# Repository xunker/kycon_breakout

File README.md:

Breakout boards for Kycon© Connectors
=====================================

[KPJX-4S](kpjx-4s_breakout/) - Configurable Breakout Board for KJPS-4S and 4S-S.

##### License and trademarks

License information can be found in [LICENSE](LICENSE).

"Kycon" is a registered trade name of Kycon, Inc.

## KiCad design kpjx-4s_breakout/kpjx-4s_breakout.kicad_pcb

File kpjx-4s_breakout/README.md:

Kycon© KPJX-4S Connector Breakout
=================================

[Schematic](images/kpjx-4s_breakout.pdf)

Mounting holes are M2.2.

## Configuration Jumpers

Use Jumper Blocks J3-J6 to map the pins from the Kycon connector to the outgoing header J2.

For example, to make Kycon pin 1 connect to J2 output pin A, pin 2 to output pin
B, pin 3 to output C, and pin 4 to GND:

Block            | Row        | State
-----------------|------------|------
J3 (Kycon pin 1) |            |
_                | 1-2 (A)    | Closed (Jumpered)
_                | 3-4 (B)    | open
_                | 5-6 (C)    | open
_                | 7-8 (GND)  | open
J4 (Kycon pin 2) |            |
_                | 1-2 (A)    | open
_                | 3-4 (B)    | Closed (Jumpered)
_                | 5-6 (C)    | open
_                | 7-8 (GND)  | open
J5 (Kycon pin 3) |            |
_                | 1-2 (A)    | open
_                | 3-4 (B)    | open
_                | 5-6 (C)    | Closed (Jumpered)
_                | 7-8 (GND)  | open
J6 (Kycon pin 4) |            |
_                | 1-2 (A)    | open
_                | 3-4 (B)    | open
_                | 5-6 (C)    | open
_                | 7-8 (GND)  | Closed (Jumpered)

Multiple Kycon pins can be connected to the same output, as long as they are the
same voltage. For example, If power coming in to the Kycon connector as +12V on
pins 1 and 3, and ground on pins 2 and 4, I could configure J3-J6 as:

Block            | Row        | State
-----------------|------------|------
J3 (Kycon pin 1) |            |
_                | 1-2 (A)    | Closed (Jumpered)
_                | 3-4 (B)    | open
_                | 5-6 (C)    | open
_                | 7-8 (GND)  | open
J4 (Kycon pin 2) |            |
_                | 1-2 (A)    | open
_                | 3-4 (B)    | open
_                | 5-6 (C)    | open
_                | 7-8 (GND)  | Closed (Jumpered)
J5 (Kycon pin 3) |            |
_                | 1-2 (A)    | Closed (Jumpered)
_                | 3-4 (B)    | open
_                | 5-6 (C)    | open
_                | 7-8 (GND)  | open
J6 (Kycon pin 4) |            |
_                | 1-2 (A)    | open
_                | 3-4 (B)    | open
_                | 5-6 (C)    | open
_                | 7-8 (GND)  | Closed (Jumpered)

This would combine both +12V pins to a single output (A) and both GND pins to
ground. In this configuration, output pins B and C are not connected.

### Credit

[Footprint for KPJX-4S](https://github.com/prusa3d/Buddy-board-MINI-PCB/blob/master/rev.1.0.0/.pretty/KPJX-4S.kicad_mod) connector is from [Prusa3D's Buddy Board Mini PCB](https://github.com/prusa3d/Buddy-board-MINI-PCB/tree/master).

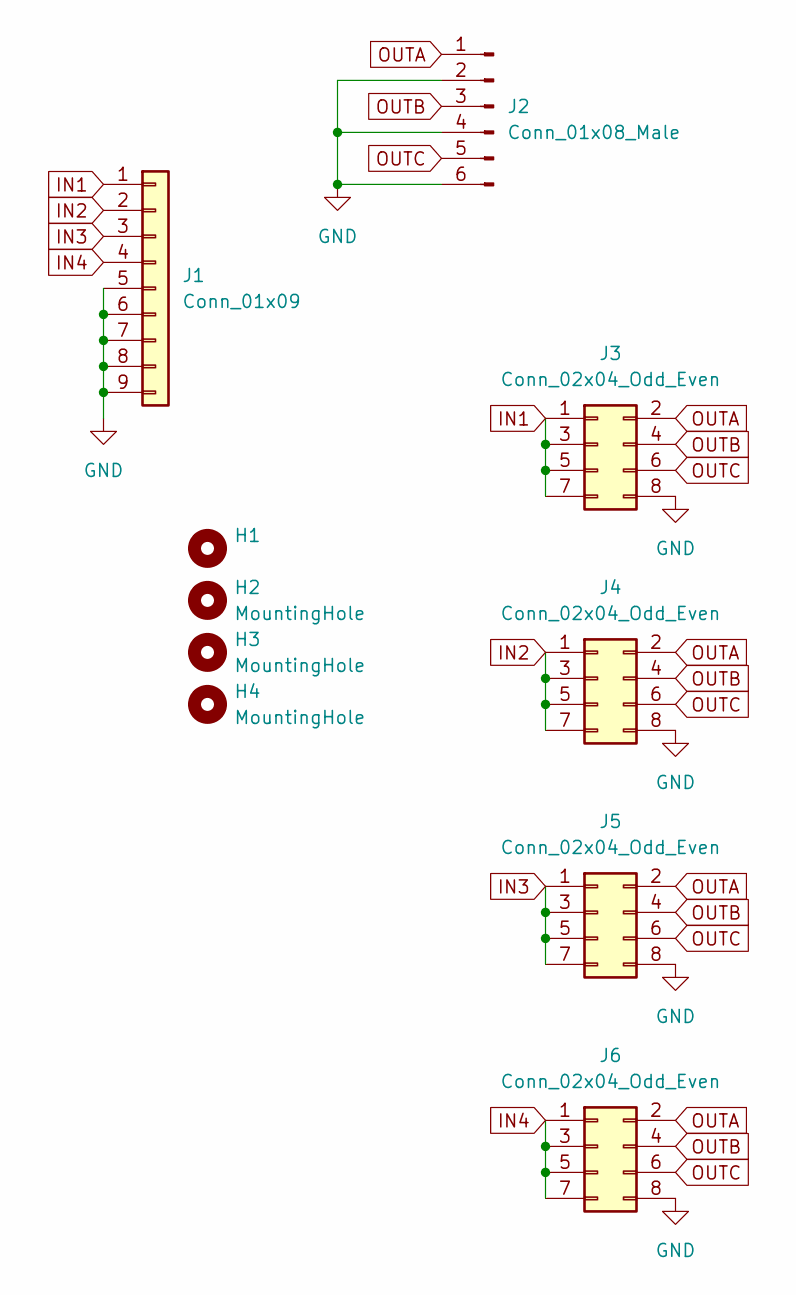
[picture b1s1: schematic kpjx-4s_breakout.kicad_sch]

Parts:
H1: (no value)
H2, H3, H4: MountingHole; MountingHole_2.2mm_M2_DIN965
J1: Conn_01x09; KPJX-4S
J2: Conn_01x08_Male; PinHeader_1x06_P2.54mm_Vertical
J3, J4, J5, J6: Conn_02x04_Odd_Even; PinHeader_2x04_P2.54mm_Vertical

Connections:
GND: J1.5, J1.6, J1.7, J1.8, J1.9, J2.2, J2.4, J2.6, J3.8, J4.8, J5.8, J6.8
IN1: J1.1, J3.1, J3.3, J3.5, J3.7
IN2: J1.2, J4.1, J4.3, J4.5, J4.7
IN3: J1.3, J5.1, J5.3, J5.5, J5.7
IN4: J1.4, J6.1, J6.3, J6.5, J6.7
OUTA: J2.1, J3.2, J4.2, J5.2, J6.2
OUTB: J2.3, J3.4, J4.4, J5.4, J6.4
OUTC: J2.5, J3.6, J4.6, J5.6, J6.6

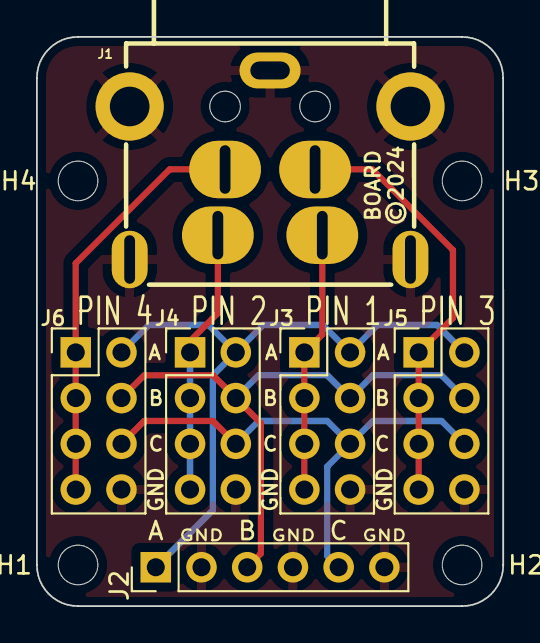
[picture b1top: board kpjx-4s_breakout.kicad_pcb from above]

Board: 2 copper layers, 25.9 x 31.6 mm, 10 parts (0 on the bottom side), 8 nets.

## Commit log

2024-06-13 add link to license
2024-06-13 add kpjs-4s from other dir
2024-06-13 Add pictures, clean up schematic
2024-06-13 fix filenames

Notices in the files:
kpjx-4s_breakout/kpjx-4s_breakout.kicad_pcb:
©2024
